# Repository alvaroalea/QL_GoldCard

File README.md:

# QL_GoldCard
A reverse engineering exercice using the Sinclair QL GoldCard Expansion Card as target

Licensed under Cern OHL-S - https://ohwr.org/cern_ohl_s_v2.txt

(The 3D Model of the PLCC chips is work of Zerover)

## WARNING: DO NOT USE THIS PROJECT IS NOT TESTED AND MISSING THINGS
This is not a functional item, it's only a exercice of reverse engineering to reinforce my skills in Kicad EDA Software.

This project match schematics found on internet, and pictures of the real interface.

* There is no know source of the JEDEC file for the Altera's CPLD
* Some IC can be deprecated and not found on market.
* No information about original has 2 or 4 copper layer, I just use 4, as I was not able to do it in only 2.

Anyway:
* There is not error or warning on the PCB and Schematics
* Schematics seen to be good
* Copper side match 1:1 pictures of internet.

For that:
* If you take the risk and do one and it work, please let me know.
* If you have the source of JEDEC file for the CPLD, please let me know.
* If you found any error in the schematic or PLC, please, let me know.

Two folder
* Original - The design as similar as posible to the Miracles design.
* Alea - new design with new footprints.

## The GoldCard Board
This card is a upgrade of the Sinclair QL computer from 1985, it provide a 68000 processor running a 16Mhz and with a bus wide of 16bit, against original 68008, 7,5Mhz and 8bits bus wide, this is theorically 4 times faster than original QL.

Provide Aditional 1920Mb of Ram (16bits) of 2048Mb installed. (128Kb are used as shadow Rom)

Include a up to 4 disk drive (3 + 1 with a add-on card) compatible with 720Kb, 1.44Mb and 2.88Mb (up to 3.2Mb depend of the format)

It have a Real Time Clock.

This was later superseded by the SuperGoldCard, that use a 68020/24Mhz and 4Mb of Ram.

There area at least 3 Version of the PCB, this is based on the lastes one, version 1 was usually yellow, version 2 and 3 was red color.

Version 1 and 2 have a capacitor solder between CLK and GND under the 68000, and a 3-pad solder jumper under the floppy controller.

CPLD have a sticker over it, "INGOT 6" for version 1 & 2, and "INGOT 5" on Golcard 3

## Comparative

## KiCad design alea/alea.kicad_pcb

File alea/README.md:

# QL GoldCard (Alea's Version)
A reverse engineering exercice using the Sinclair QL GoldCard Expansion Card as target

Licensed under Cern OHL-S - https://ohwr.org/cern_ohl_s_v2.txt

(The 3D Model of the PLCC chips is work of Zerover)

## WARNING: DO NOT USE THIS PROJECT IS NOT TESTED AND MISSING THINGS
This is not a functional item, it's only a exercice of reverse engineering to reinforce my skills in Kicad EDA Software.

* Use memory SIP-24 easy to found.
* No IC over IC
* small but in market battery socket
* 9V/5V jumpers for use with aurora or backplanes.

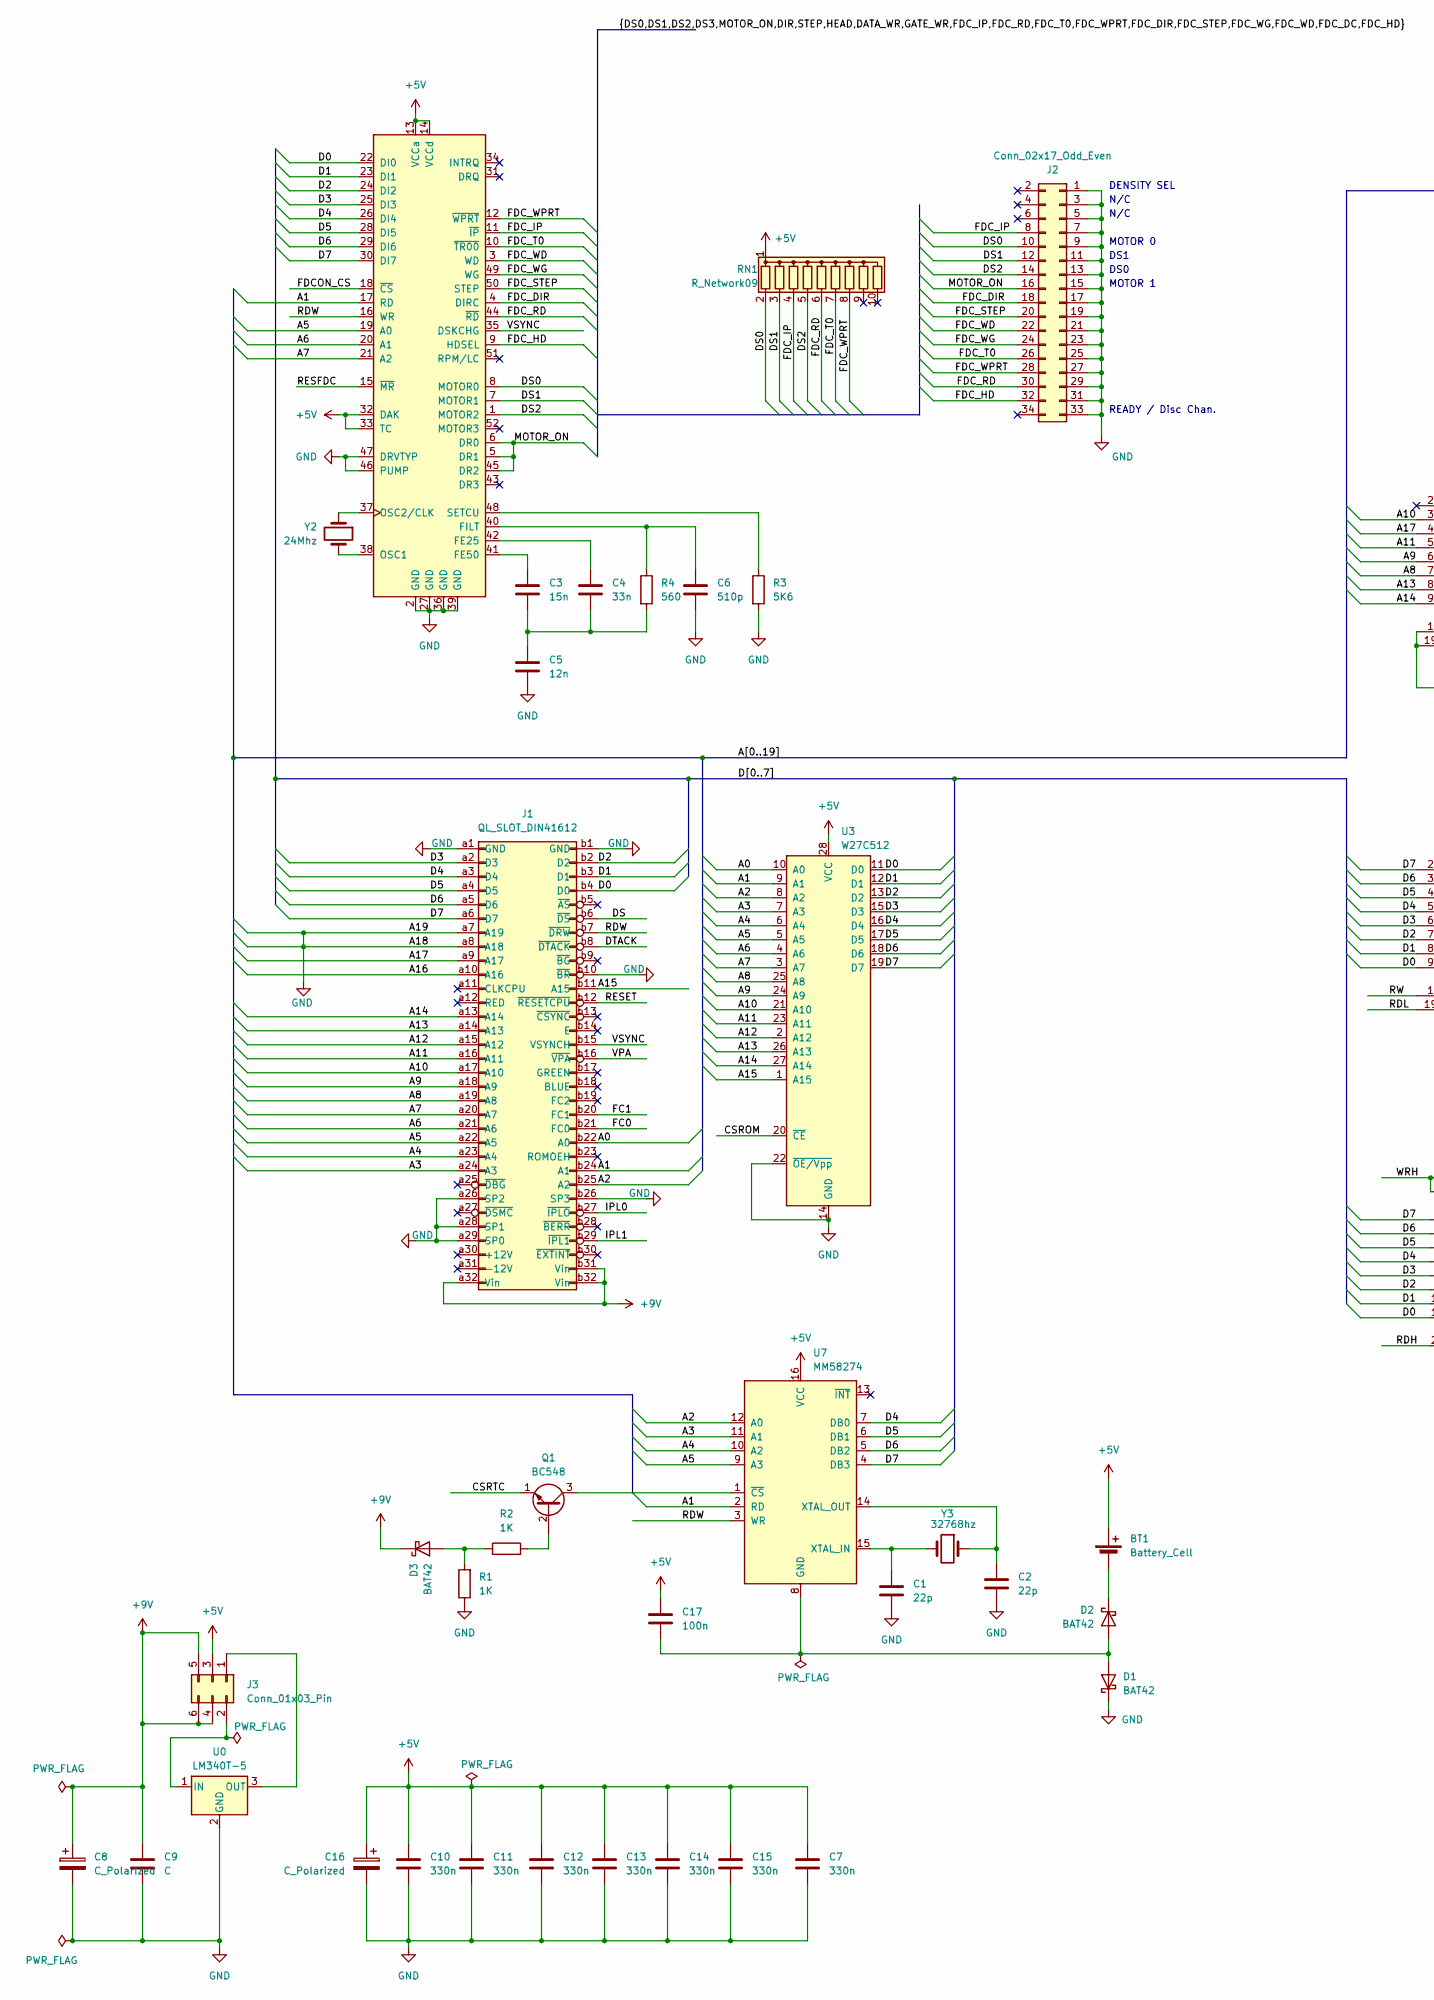
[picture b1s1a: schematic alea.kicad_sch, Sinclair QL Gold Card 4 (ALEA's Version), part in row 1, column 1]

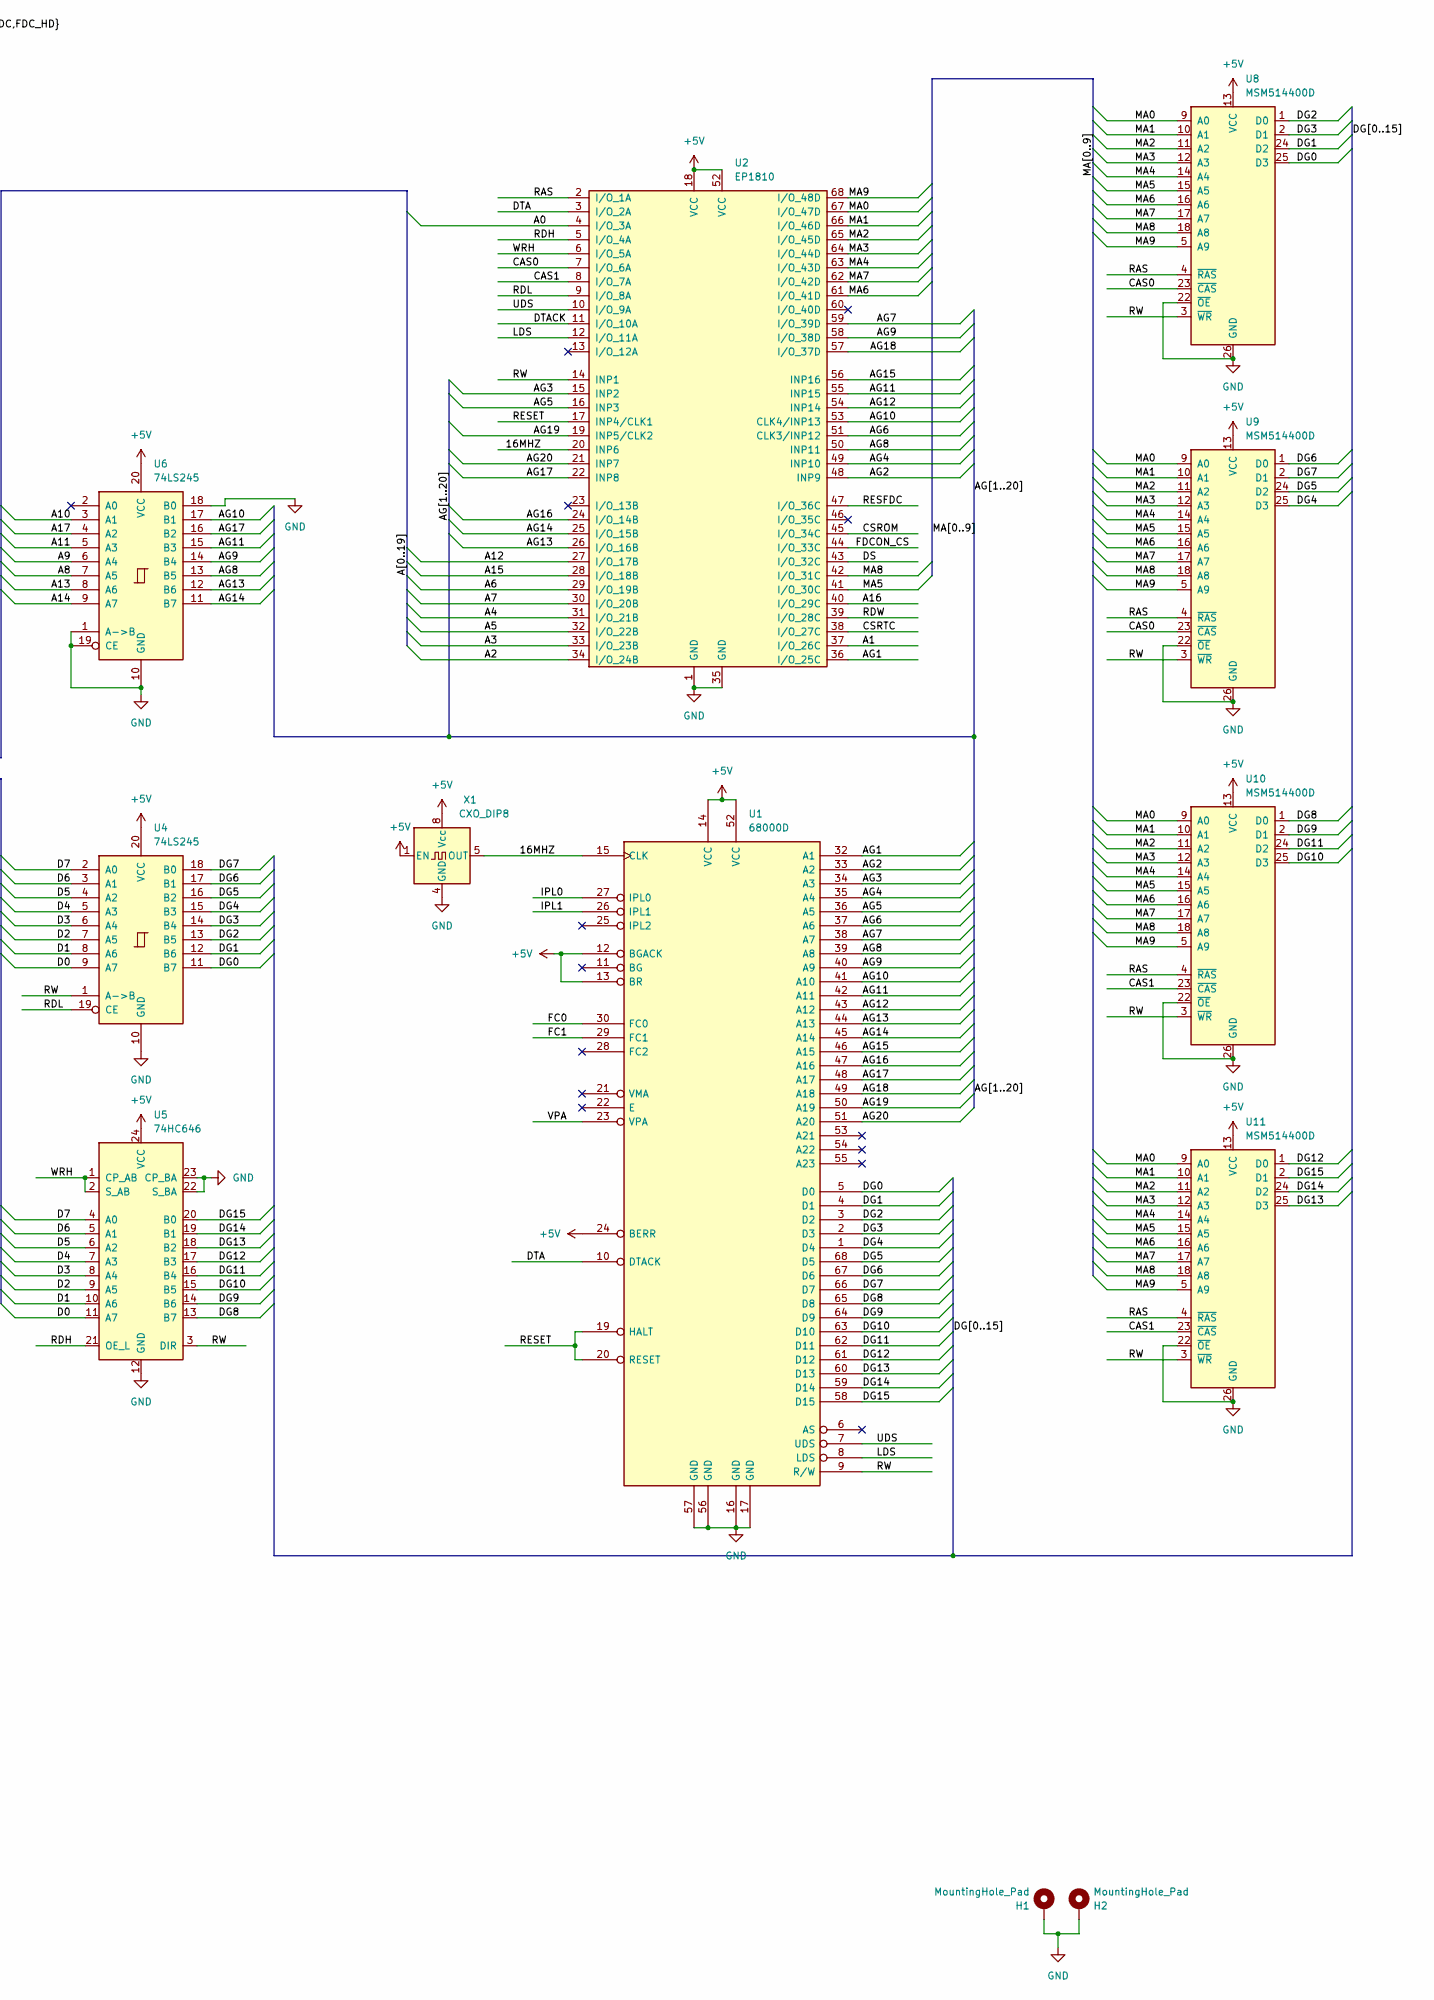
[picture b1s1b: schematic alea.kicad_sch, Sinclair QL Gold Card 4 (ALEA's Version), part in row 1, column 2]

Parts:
BT1: Battery_Cell; BatteryHolder_Keystone_500
C1, C2: 22p; C_Disc_D3.0mm_W1.6mm_P2.50mm
C3: 15n; C_Disc_D4.3mm_W1.9mm_P5.00mm
C4: 33n; C_Disc_D4.3mm_W1.9mm_P5.00mm
C5: 12n; C_Disc_D4.3mm_W1.9mm_P5.00mm
C6: 510p; C_Disc_D4.3mm_W1.9mm_P5.00mm
C7, C10, C11, C12, C13, C14, C15: 330n; C_Disc_D4.3mm_W1.9mm_P5.00mm
C8: C_Polarized; CP_Radial_D7.5mm_P2.50mm
C9: C; C_Disc_D4.3mm_W1.9mm_P5.00mm
C16: C_Polarized; CP_Radial_D8.0mm_P3.50mm
C17: 100n; C_Disc_D4.3mm_W1.9mm_P5.00mm
D1, D2, D3: BAT42; D_DO-35_SOD27_P7.62mm_Horizontal
H1, H2: MountingHole_Pad; MountingHole_2.5mm_Pad_Via
J1: QL_SLOT_DIN41612; DIN41612_B_2x32_Female_Horizontal_THT
J2: Conn_02x17_Odd_Even; PinHeader_2x17_P2.54mm_Horizontal
J3: Conn_01x03_Pin; PinHeader_2x03_P2.54mm_Vertical
Q1: BC548; TO-18-3
R1, R2: 1K; R_Axial_DIN0204_L3.6mm_D1.6mm_P7.62mm_Horizontal
R3: 5K6; R_Axial_DIN0204_L3.6mm_D1.6mm_P7.62mm_Horizontal
R4: 560; R_Axial_DIN0204_L3.6mm_D1.6mm_P7.62mm_Horizontal
RN1: R_Network09; R_Array_SIP10
U0: LM340T-5; CONV_TSR_2-2450
U1: 68000D; PLCC-68_THT-Socket
U2: EP1810; PLCC-68_THT-Socket
U3: W27C512; DIP-28_W15.24mm
U4, U6: 74LS245; DIP-20_W7.62mm
U5: 74HC646; DIP-24_W7.62mm
U7: MM58274; DIP-16_W7.62mm
U8, U9, U10, U11: MSM514400D; SOJ-26_7.62x18.415mm_P1.27mm
U12: DP4873V; PLCC-52_THT-Socket
X1: CXO_DIP8; Oscillator_SeikoEpson_SG-8002DC
Y2: 24Mhz; Crystal_HC49-U_Vertical
Y3: 32768hz; Crystal_AT310_D3.0mm_L10.0mm_Vertical

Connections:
+5V: BT1.1 (+), C7.1, C10.1, C11.1, C12.1, C13.1, C14.1, C15.1, C16.1, C17.1, J3.3, RN1.1 (common), U1.12 (BGACK), U1.13 (BR), U1.14 (VCC), U1.24 (BERR), U1.52 (VCC), U2.18 (VCC), U2.52 (VCC), U3.28 (VCC), U4.20 (VCC), U5.24 (VCC), U6.20 (VCC), U7.16 (VCC), U8.13 (VCC), U9.13 (VCC), U10.13 (VCC), U11.13 (VCC), U12.13 (VCCa), U12.14 (VCCd), U12.32 (DAK), U12.33 (TC), X1.1 (EN), X1.8 (Vcc)
+9V: C8.1, C9.1, D3.1 (K), J1.a32 (Vin), J1.b31 (Vin), J1.b32 (Vin), J3.4, J3.5, J3.6
/16MHZ: U1.15 (CLK), U2.20 (INP6), X1.5 (OUT)
/A0: J1.b22 (A0), U2.4 (I/O_3A), U3.10 (A0)
/A1: J1.b24 (A1), U2.37 (I/O_26C), U3.9 (A1), U7.2 (RD), U12.17 (RD)
/A2: J1.b25 (A2), U2.34 (I/O_24B), U3.8 (A2), U7.12 (A0)
/A3: J1.a24 (A3), U2.33 (I/O_23B), U3.7 (A3), U7.11 (A1)
/A4: J1.a23 (A4), U2.31 (I/O_21B), U3.6 (A4), U7.10 (A2)
/A5: J1.a22 (A5), U2.32 (I/O_22B), U3.5 (A5), U7.9 (A3), U12.19 (A0)
/A6: J1.a21 (A6), U2.29 (I/O_19B), U3.4 (A6), U12.20 (A1)
/A7: J1.a20 (A7), U2.30 (I/O_20B), U3.3 (A7), U12.21 (A2)
/A8: J1.a19 (A8), U3.25 (A8), U6.7 (A5)
/A9: J1.a18 (A9), U3.24 (A9), U6.6 (A4)
/A10: J1.a17 (A10), U3.21 (A10), U6.3 (A1)
/A11: J1.a16 (A11), U3.23 (A11), U6.5 (A3)
/A12: J1.a15 (A12), U2.27 (I/O_17B), U3.2 (A12)
/A13: J1.a14 (A13), U3.26 (A13), U6.8 (A6)
/A14: J1.a13 (A14), U3.27 (A14), U6.9 (A7)
/A15: J1.b11 (A15), U2.28 (I/O_18B), U3.1 (A15)
/A16: J1.a10 (A16), U2.40 (I/O_29C)
/A17: J1.a9 (A17), U6.4 (A2)
/AG1: U1.32 (A1), U2.36 (I/O_25C)
/AG2: U1.33 (A2), U2.48 (INP9)
/AG3: U1.34 (A3), U2.15 (INP2)
/AG4: U1.35 (A4), U2.49 (INP10)
/AG5: U1.36 (A5), U2.16 (INP3)
/AG6: U1.37 (A6), U2.51 (CLK3/INP12)
/AG7: U1.38 (A7), U2.59 (I/O_39D)
/AG8: U1.39 (A8), U2.50 (INP11), U6.13 (B5)
/AG9: U1.40 (A9), U2.58 (I/O_38D), U6.14 (B4)
/AG10: U1.41 (A10), U2.53 (CLK4/INP13), U6.17 (B1)
/AG11: U1.42 (A11), U2.55 (INP15), U6.15 (B3)
/AG12: U1.43 (A12), U2.54 (INP14)
/AG13: U1.44 (A13), U2.26 (I/O_16B), U6.12 (B6)
/AG14: U1.45 (A14), U2.25 (I/O_15B), U6.11 (B7)
/AG15: U1.46 (A15), U2.56 (INP16)
/AG16: U1.47 (A16), U2.24 (I/O_14B)
/AG17: U1.48 (A17), U2.22 (INP8), U6.16 (B2)
/AG18: U1.49 (A18), U2.57 (I/O_37D)
/AG19: U1.50 (A19), U2.19 (INP5/CLK2)
/AG20: U1.51 (A20), U2.21 (INP7)
/CAS0: U2.7 (I/O_6A), U8.23 (~CAS), U9.23 (~CAS)
/CAS1: U2.8 (I/O_7A), U10.23 (~CAS), U11.23 (~CAS)
/CSROM: U2.45 (I/O_34C), U3.20 (~CE)
/CSRTC: Q1.1 (E), U2.38 (I/O_27C)
/D0: J1.b4 (D0), U3.11 (D0), U4.9 (A7), U5.11 (A7), U12.22 (DI0)
/D1: J1.b3 (D1), U3.12 (D1), U4.8 (A6), U5.10 (A6), U12.23 (DI1)
/D2: J1.b2 (D2), U3.13 (D2), U4.7 (A5), U5.9 (A5), U12.24 (DI2)
/D3: J1.a2 (D3), U3.15 (D3), U4.6 (A4), U5.8 (A4), U12.25 (DI3)
/D4: J1.a3 (D4), U3.16 (D4), U4.5 (A3), U5.7 (A3), U7.7 (DB0), U12.26 (DI4)
/D5: J1.a4 (D5), U3.17 (D5), U4.4 (A2), U5.6 (A2), U7.6 (DB1), U12.28 (DI5)
/D6: J1.a5 (D6), U3.18 (D6), U4.3 (A1), U5.5 (A1), U7.5 (DB2), U12.29 (DI6)
/D7: J1.a6 (D7), U3.19 (D7), U4.2 (A0), U5.4 (A0), U7.4 (DB3), U12.30 (DI7)
/DG0: U1.5 (D0), U4.11 (B7), U8.25 (D3)
/DG1: U1.4 (D1), U4.12 (B6), U8.24 (D2)
/DG2: U1.3 (D2), U4.13 (B5), U8.1 (D0)
/DG3: U1.2 (D3), U4.14 (B4), U8.2 (D1)
/DG4: U1.1 (D4), U4.15 (B3), U9.25 (D3)
/DG5: U1.68 (D5), U4.16 (B2), U9.24 (D2)
/DG6: U1.67 (D6), U4.17 (B1), U9.1 (D0)
/DG7: U1.66 (D7), U4.18 (B0), U9.2 (D1)
/DG8: U1.65 (D8), U5.13 (B7), U10.1 (D0)
/DG9: U1.64 (D9), U5.14 (B6), U10.2 (D1)
/DG10: U1.63 (D10), U5.15 (B5), U10.25 (D3)
/DG11: U1.62 (D11), U5.16 (B4), U10.24 (D2)
/DG12: U1.61 (D12), U5.17 (B3), U11.1 (D0)
/DG13: U1.60 (D13), U5.18 (B2), U11.25 (D3)
/DG14: U1.59 (D14), U5.19 (B1), U11.24 (D2)
/DG15: U1.58 (D15), U5.20 (B0), U11.2 (D1)
/DS: J1.b6 (~DS), U2.43 (I/O_32C)
/DS0: J2.10, RN1.2 (R1), U12.8 (MOTOR0)
/DS1: J2.12, RN1.3 (R2), U12.7 (MOTOR1)
/DS2: J2.14, RN1.5 (R4), U12.1 (MOTOR2)
/DTA: U1.10 (DTACK), U2.3 (I/O_2A)
/DTACK: J1.b8 (~DTACK), U2.11 (I/O_10A)
/FC0: J1.b21 (FC0), U1.30 (FC0)
/FC1: J1.b20 (FC1), U1.29 (FC1)
/FDCON_CS: U2.44 (I/O_33C), U12.18 (~CS)
/FDC_DIR: J2.18, U12.4 (DIRC)
/FDC_HD: J2.32, U12.9 (HDSEL)
/FDC_IP: J2.8, RN1.4 (R3), U12.11 (~IP)
/FDC_RD: J2.30, RN1.6 (R5), U12.44 (~RD)
/FDC_STEP: J2.20, U12.50 (STEP)
/FDC_T0: J2.26, RN1.7 (R6), U12.10 (~TR00)
/FDC_WD: J2.22, U12.3 (WD)
/FDC_WG: J2.24, U12.49 (WG)
/FDC_WPRT: J2.28, RN1.8 (R7), U12.12 (~WPRT)
/IPL0: J1.b27 (~IPLO), U1.27 (IPL0)
/IPL1: J1.b29 (~IPL1), U1.26 (IPL1)
/LDS: U1.8 (LDS), U2.12 (I/O_11A)
/MA0: U2.67 (I/O_47D), U8.9 (A0), U9.9 (A0), U10.9 (A0), U11.9 (A0)
/MA1: U2.66 (I/O_46D), U8.10 (A1), U9.10 (A1), U10.10 (A1), U11.10 (A1)
/MA2: U2.65 (I/O_45D), U8.11 (A2), U9.11 (A2), U10.11 (A2), U11.11 (A2)
/MA3: U2.64 (I/O_44D), U8.12 (A3), U9.12 (A3), U10.12 (A3), U11.12 (A3)
/MA4: U2.63 (I/O_43D), U8.14 (A4), U9.14 (A4), U10.14 (A4), U11.14 (A4)
/MA5: U2.41 (I/O_30C), U8.15 (A5), U9.15 (A5), U10.15 (A5), U11.15 (A5)
/MA6: U2.61 (I/O_41D), U8.16 (A6), U9.16 (A6), U10.16 (A6), U11.16 (A6)
/MA7: U2.62 (I/O_42D), U8.17 (A7), U9.17 (A7), U10.17 (A7), U11.17 (A7)
/MA8: U2.42 (I/O_31C), U8.18 (A8), U9.18 (A8), U10.18 (A8), U11.18 (A8)
/MA9: U2.68 (I/O_48D), U8.5 (A9), U9.5 (A9), U10.5 (A9), U11.5 (A9)
/MOTOR_ON: J2.16, U12.5 (DR1), U12.6 (DR0), U12.45 (DR2)
/RAS: U2.2 (I/O_1A), U8.4 (~RAS), U9.4 (~RAS), U10.4 (~RAS), U11.4 (~RAS)
/RDH: U2.5 (I/O_4A), U5.21 (OE_L)
/RDL: U2.9 (I/O_8A), U4.19 (CE)
/RDW: J1.b7 (~DRW), U2.39 (I/O_28C), U7.3 (WR), U12.16 (WR)
/RESET: J1.b12 (~RESETCPU), U1.19 (HALT), U1.20 (RESET), U2.17 (INP4/CLK1)
/RESFDC: U2.47 (I/O_36C), U12.15 (~MR)
/RW: U1.9 (R/W), U2.14 (INP1), U4.1 (A->B), U5.3 (DIR), U8.3 (~WR), U9.3 (~WR), U10.3 (~WR), U11.3 (~WR)
/UDS: U1.7 (UDS), U2.10 (I/O_9A)
/VPA: J1.b16 (~VPA), U1.23 (VPA)
/VSYNC: J1.b15 (VSYNCH), U12.35 (DSKCHG)
/WRH: U2.6 (I/O_5A), U5.1 (CP_AB), U5.2 (S_AB)
GND: C1.2, C2.2, C5.2, C6.2, C7.2, C8.2, C9.2, C10.2, C11.2, C12.2, C13.2, C14.2, C15.2, C16.2, D1.1 (K), H1.1, H2.1, J1.a1 (GND), J1.a7 (A19), J1.a8 (A18), J1.a26 (SP2), J1.a28 (SP1), J1.a29 (SP0), J1.b1 (GND), J1.b10 (~BR), J1.b26 (SP3), J2.1, J2.3, J2.5, J2.7, J2.9, J2.11, J2.13, J2.15, J2.17, J2.19, J2.21, J2.23, J2.25, J2.27, J2.29, J2.31, J2.33, R1.1, R3.2, U0.2 (GND), U1.16 (GND), U1.17 (GND), U1.56 (GND), U1.57 (GND), U2.1 (GND), U2.35 (GND), U3.14 (GND), U3.22 (~OE/Vpp), U4.10 (GND), U5.12 (GND), U5.22 (S_BA), U5.23 (CP_BA), U6.1 (A->B), U6.10 (GND), U6.18 (B0), U6.19 (CE), U8.22 (~OE), U8.26 (GND), U9.22 (~OE), U9.26 (GND), U10.22 (~OE), U10.26 (GND), U11.22 (~OE), U11.26 (GND), U12.2 (GND), U12.27 (GND), U12.36 (GND), U12.39 (GND), U12.46 (PUMP), U12.47 (DRVTYP), X1.4 (GND)
unnamed: BT1.2 (-), D2.1 (K)
unnamed: C3.2, C4.2, C5.1, R4.2
unnamed: C17.2, D1.2 (A), D2.2 (A), U7.8 (GND)
unnamed: D3.2 (A), R1.2, R2.1
unnamed: J3.1, U0.3 (OUT)
unnamed: J3.2, U0.1 (IN)
unnamed: Q1.2 (B), R2.2
unnamed: Q1.3 (C), U7.1 (~CS)
unnamed: C1.1, U7.15 (XTAL_IN), Y3.2
unnamed: C2.1, U7.14 (XTAL_OUT), Y3.1
unnamed: C4.1, U12.42 (FE25)
unnamed: C3.1, U12.41 (FE50)
unnamed: C6.1, R4.1, U12.40 (FILT)
unnamed: U12.38 (OSC1), Y2.2
unnamed: U12.37 (OSC2/CLK), Y2.1
unnamed: R3.1, U12.48 (SETCU)

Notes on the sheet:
N/C
DENSITY SEL
MOTOR 0
MOTOR 1
DS0
READY / Disc Chan.
DS1

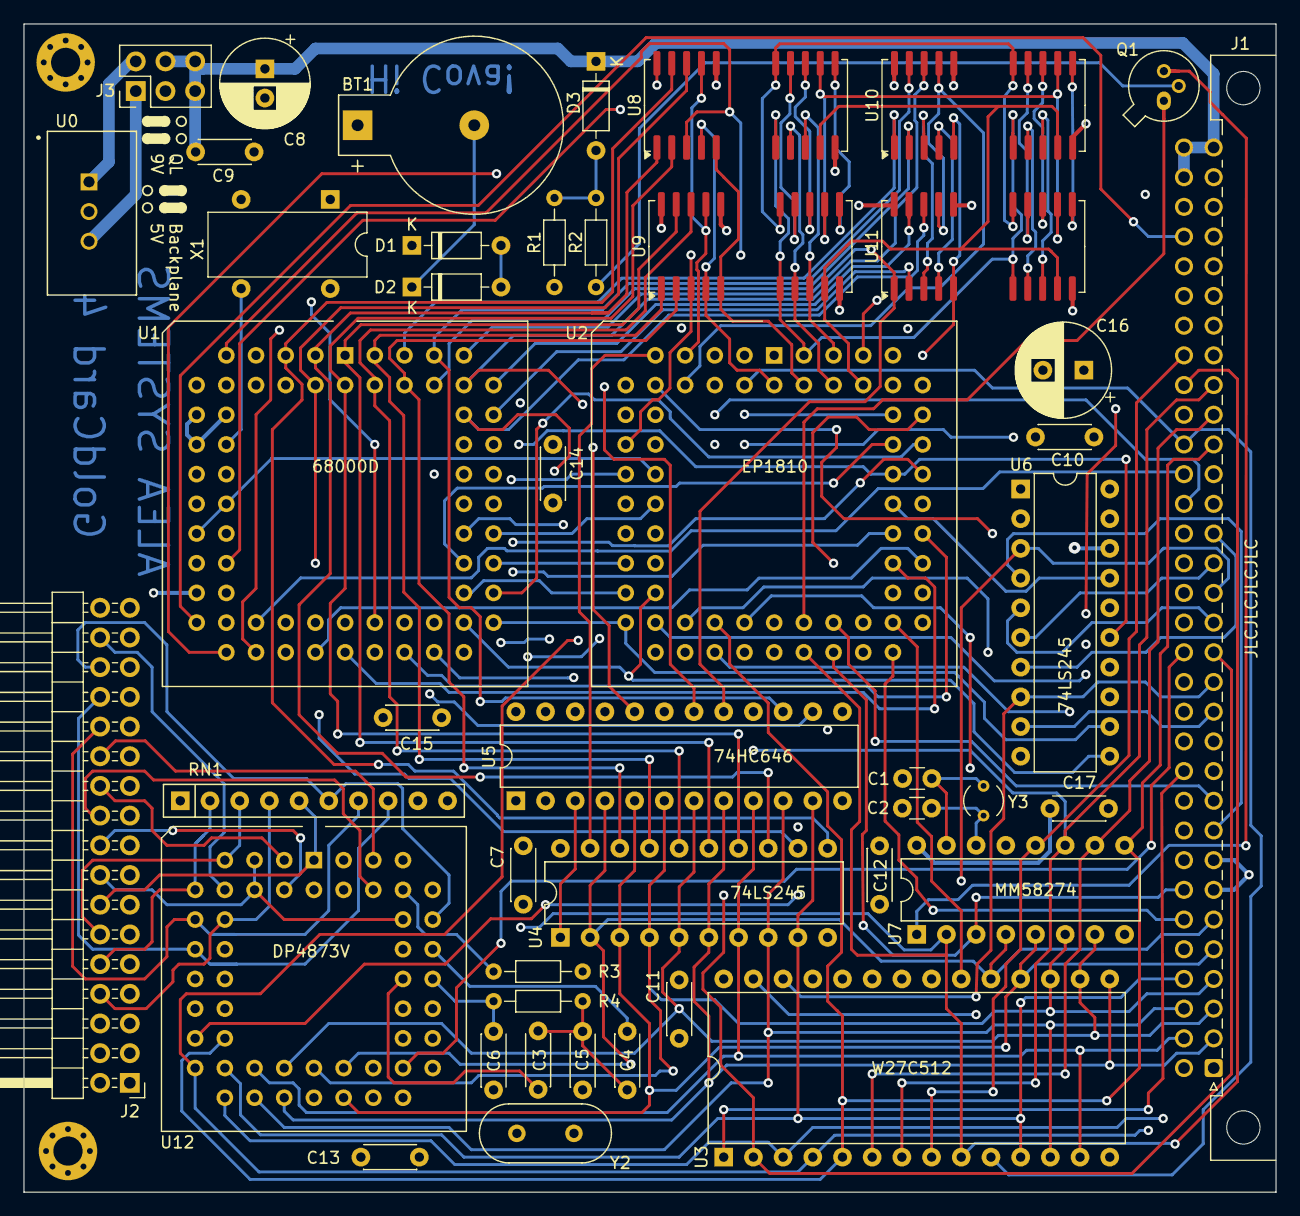
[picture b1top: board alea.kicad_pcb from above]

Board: 4 copper layers, 107.1 x 99.9 mm, 48 parts (0 on the bottom side), 129 nets.

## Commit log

2024-04-14 Initial
2025-06-22 fix fault in pcb of FDC and add orignal + alea versions
2025-06-25 remove last extra vias
2025-06-29 2025/06 update
2025-06-30 update again for bad FDC pinout
2025-07-05 fix values
2025-08-05 small update in alea
